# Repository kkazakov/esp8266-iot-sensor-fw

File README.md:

# esp8266-iot-sensor-fw
ESP8266-based IOT sensor firmware

More info available here: http://dev.drun.net/2018/05/21/measuring-temperature-humidity-pressure-esp8266/

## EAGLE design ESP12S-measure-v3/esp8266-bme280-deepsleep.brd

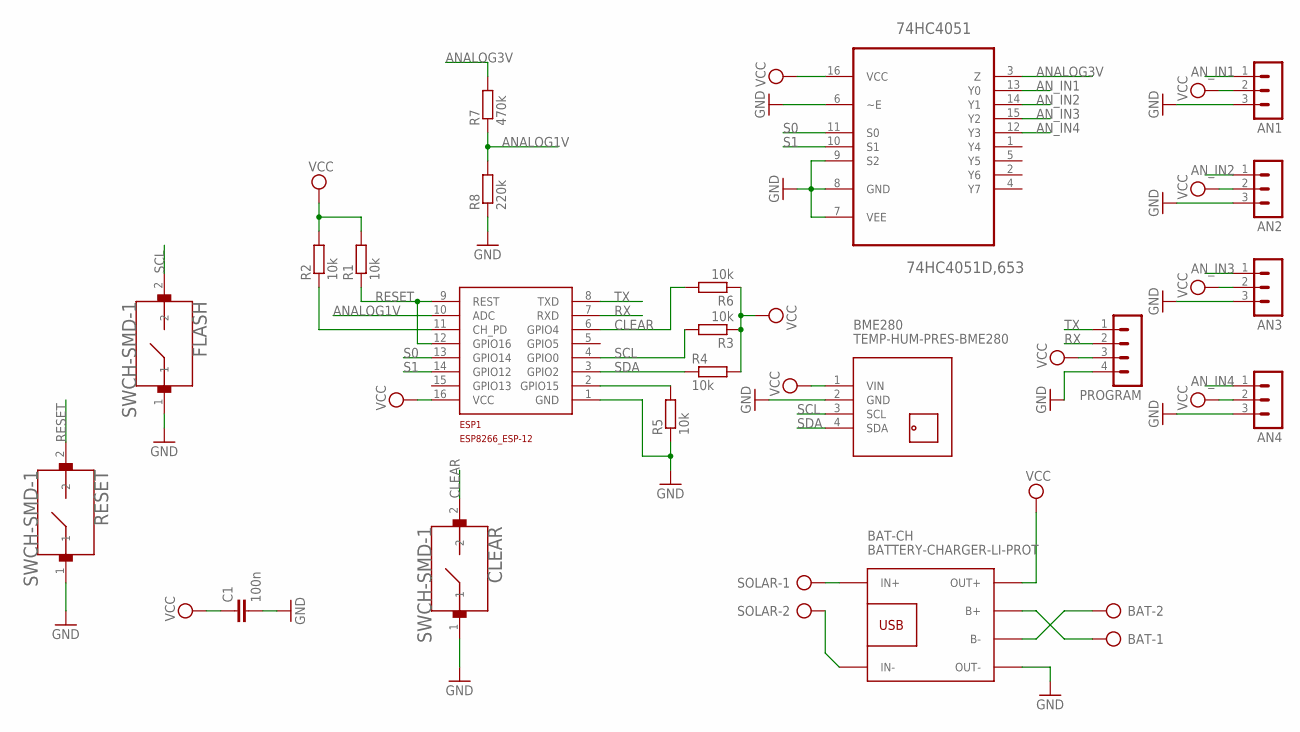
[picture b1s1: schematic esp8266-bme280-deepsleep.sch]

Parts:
74HC4051: 74HC4051D,653; SOIC127P600X175-16N
AN1, AN2, AN3, AN4: MA03-1
BAT: PWR_CONN_KK; PWR_CONN_KK_5MM
BAT-CH: BATTERY-CHARGER-LI-PROT
BME280: TEMP-HUM-PRES-BME280
C1: 100n; C2.5-3
CLEAR: SWCH-SMD-1
ESP1: ESP8266_ESP-12; ESP8266-ESP12
FLASH: SWCH-SMD-1
PROGRAM: MA04-1
R1, R2, R3, R4, R5, R6: 10k; 0204/7
R7: 470k; 0204/7
R8: 220k; 0204/7
RESET: SWCH-SMD-1
SOLAR: PWR_CONN_KK; PWR_CONN_KK_5MM

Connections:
ANALOG1V: ESP1.10 (ADC), R7.1, R8.2
ANALOG3V: 74HC4051.3 (Z), R7.2
AN_IN1: 74HC4051.13 (Y0), AN1.1
AN_IN2: 74HC4051.14 (Y1), AN2.1
AN_IN3: 74HC4051.15 (Y2), AN3.1
AN_IN4: 74HC4051.12 (Y3), AN4.1
CLEAR: CLEAR.2, ESP1.6 (GPIO4), R6.2
GND: 74HC4051.6 (~E), 74HC4051.7 (VEE), 74HC4051.8 (GND), 74HC4051.9 (S2), AN1.3, AN2.3, AN3.3, AN4.3, BAT-CH.OUT-, BME280.2 (GND), C1.2, CLEAR.1, ESP1.1 (GND), FLASH.1, PROGRAM.4, R5.1, R8.1, RESET.1
unnamed: ESP1.11 (CH_PD), R2.1
unnamed: BAT.1, BAT-CH.B+
unnamed: BAT.2, BAT-CH.B-
unnamed: BAT-CH.IN+, SOLAR.1
unnamed: BAT-CH.IN-, SOLAR.2
unnamed: ESP1.2 (GPIO15), R5.2
RESET: ESP1.9 (REST), ESP1.12 (GPIO16), R1.1, RESET.2
RX: ESP1.7 (RXD), PROGRAM.2
S0: 74HC4051.11 (S0), ESP1.13 (GPIO14)
S1: 74HC4051.10 (S1), ESP1.14 (GPIO12)
SCL: BME280.3 (SCL), ESP1.4 (GPIO0), FLASH.2, R3.2
SDA: BME280.4 (SDA), ESP1.3 (GPIO2), R4.1
TX: ESP1.8 (TXD), PROGRAM.1
VCC: 74HC4051.16 (VCC), AN1.2, AN2.2, AN3.2, AN4.2, BAT-CH.OUT+, BME280.1 (VIN), C1.1, ESP1.16 (VCC), PROGRAM.3, R1.2, R2.2, R3.1, R4.2, R6.1

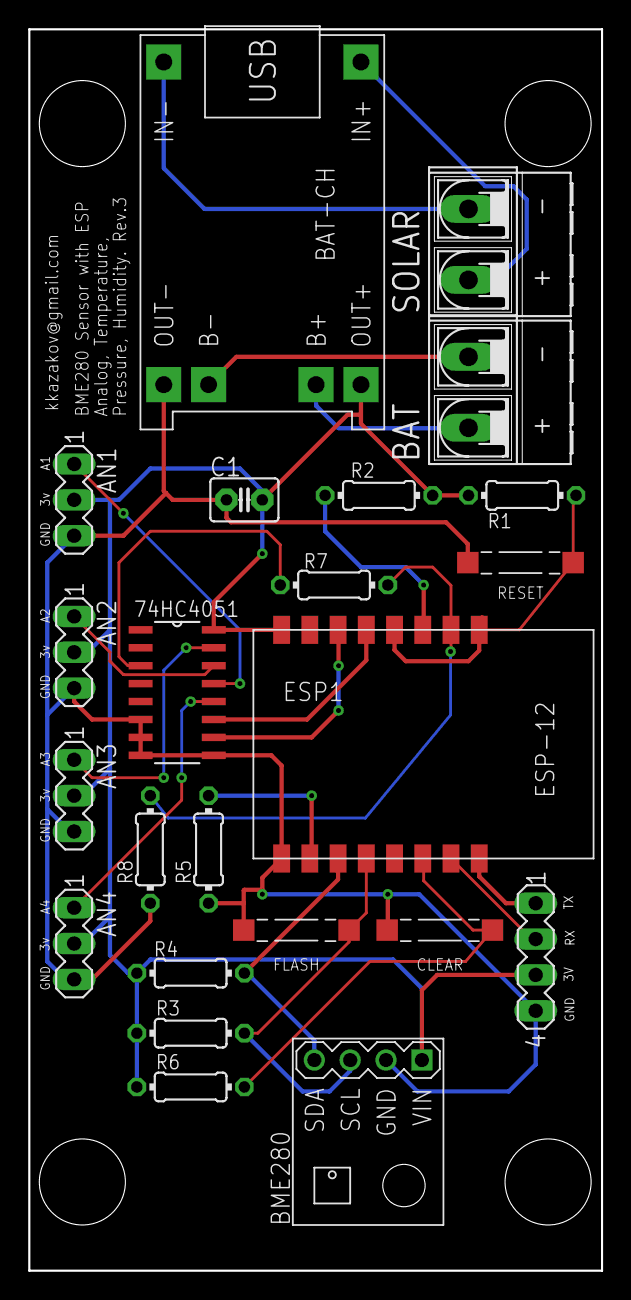
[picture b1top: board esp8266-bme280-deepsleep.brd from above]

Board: 2 copper layers, 40.6 x 87.9 mm, 23 parts (0 on the bottom side), 22 nets.

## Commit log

2018-05-20 added the first version of esp-12s + bme280 or bmp180 sensors, battery charging, deep sleep enabled and solar panel input. It's test and works.
2018-05-21 activated deep sleep mode, added box (enclosure) specification
2018-05-21 added second version (prototype) schematics + board with 4 analog inputs
2018-05-21 fixes
2018-05-21 The board now goes to deep sleep and not in soft ap, if the ssid cannot be found. This is crucial, so that it does not drain the battery.
2018-05-21 updated readme with link
2018-05-23 Added core ThingSpeak library
2018-05-23 Some refactoring, added ThingSpeak configuration and logic ( IT'S NOT YET TESTED!)
2018-05-30 fixed thingspeak save in the form
2018-05-30 optimizations, ThingSpeak sending works now
2018-05-30 Code cleanup, fix for going into deepsleep too soon and not registering event to ThingSpeak
2019-04-13 Fix for BMP180
2019-04-13 Ignoring vscode files
2019-04-21 Third revision

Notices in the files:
parts and their libraries:
diy-modules: Released under the Creative Commons Attribution 4.0 International License: http://creativecommons.org/licenses/by/4.0
